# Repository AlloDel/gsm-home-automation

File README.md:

# gsm-home-automation
a simple home automatiion system using a GSM module designed with kicad 5 and recently updated for kicad6

PDFs and images of schematic and 3d render are in the /docs directory

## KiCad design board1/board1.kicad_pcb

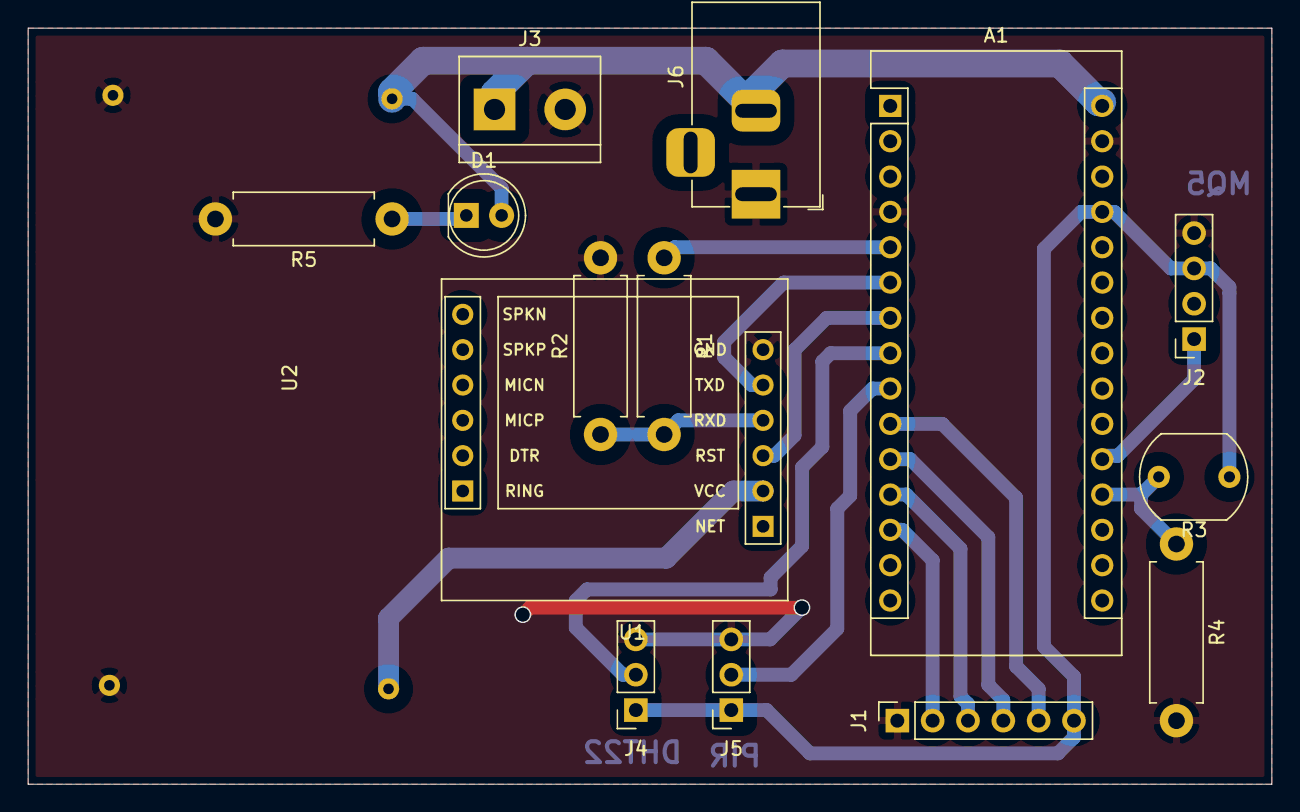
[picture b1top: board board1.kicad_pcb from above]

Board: 2 copper layers, 89.4 x 54.4 mm, 15 parts (0 on the bottom side), 17 nets.

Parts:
A1: Arduino_Nano_v3.x; Arduino_Nano
D1: LED_Small; LED_D5.0mm
J1: RELAY MODULE; PinSocket_1x06_P2.54mm_Vertical
J2: MQ5; PinSocket_1x04_P2.54mm_Vertical
J3: Screw_Terminal_01x02; TerminalBlock_bornier-2_P5.08mm
J4: DHT22; PinSocket_1x03_P2.54mm_Vertical
J5: PIR; PinSocket_1x03_P2.54mm_Vertical
J6: Barrel_Jack; BarrelJack_Horizontal
R1, R2, R4, R5: R_Small; R_Axial_DIN0411_L9.9mm_D3.6mm_P12.70mm_Horizontal
R3: R_PHOTO; R_LDR_7x6mm_P5.1mm_Vertical
U1: SIM800L
U2: buckconverter; backconverter

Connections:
+4V: U1.1, U2.3
+5V: A1.27, J1.6, J2.3, J4.1, J5.1, R3.1
/5V_GSM_RX: A1.5, R1.1
/APPLIANCE: A1.11, J1.4
/ELECTRIC_FAN: A1.10, J1.5
/GAS_SENSE: A1.20, J2.1
/GSM_RST: A1.7, U1.2
/GSM_RX: R1.2, R2.1, U1.3
/GSM_TX: A1.6, U1.4
/INSIDE_BULB: A1.12, J1.3
/LDR_SENSE: A1.19, R3.2, R4.1
/OUTSIDE_BULB: A1.13, J1.2
/PIR_SENSE: A1.9, J5.2
/TEMP_SENSE: A1.8, J4.2
GND: A1.4, A1.29, J1.1, J2.4, J3.2, J4.3, J5.3, J6.1, R2.2, R4.2, R5.2, U1.5, U2.2, U2.4
unnamed: D1.1, R5.1
VCC: A1.30, D1.2, J3.1, J6.2, U2.1
